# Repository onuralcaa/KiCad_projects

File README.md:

# Repository Hakkında 

Udemy - Donanım Tasarımı adlı eğitim çalışmaları.

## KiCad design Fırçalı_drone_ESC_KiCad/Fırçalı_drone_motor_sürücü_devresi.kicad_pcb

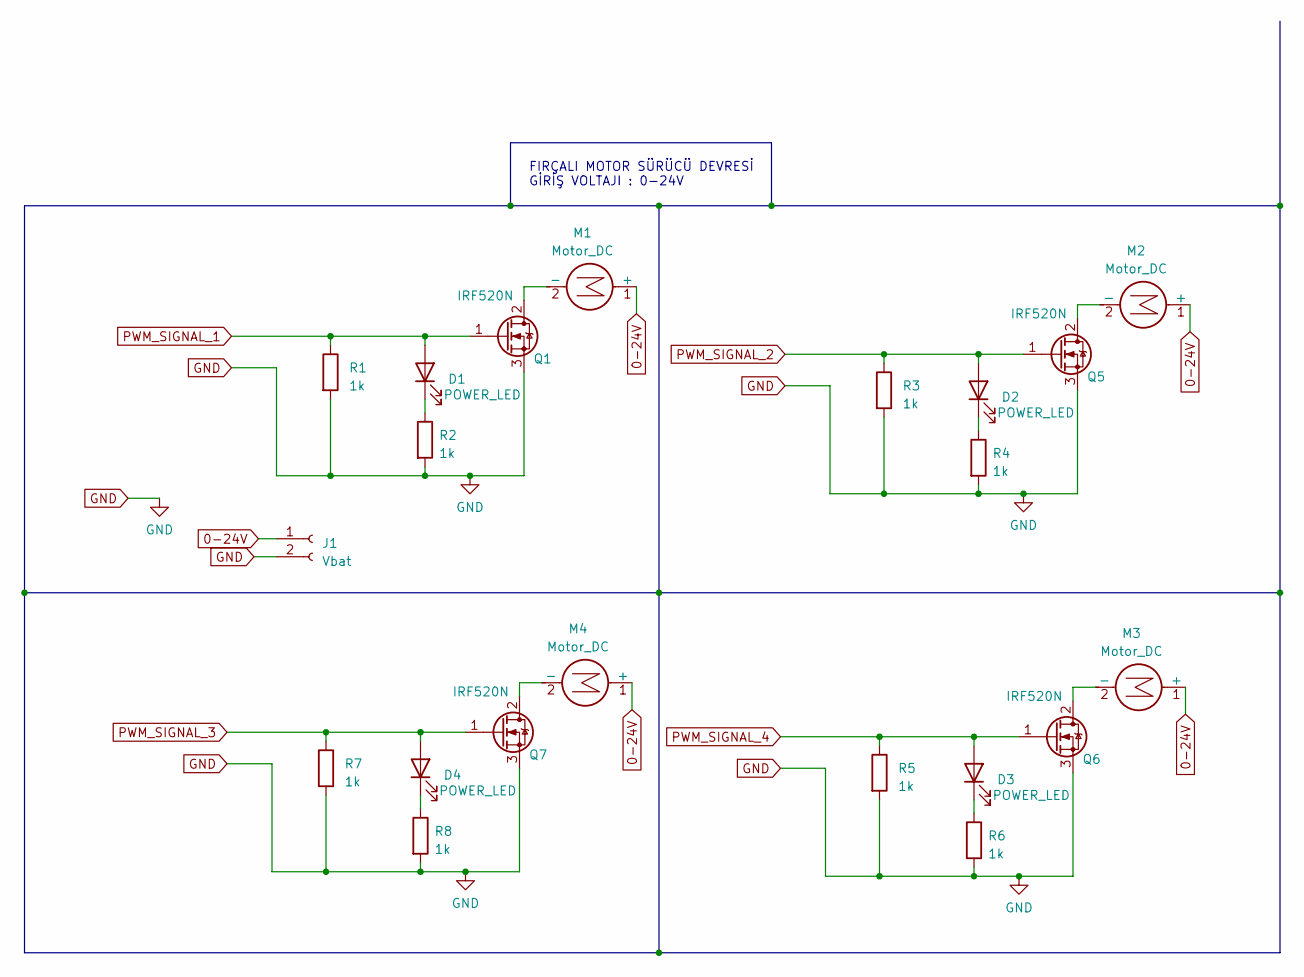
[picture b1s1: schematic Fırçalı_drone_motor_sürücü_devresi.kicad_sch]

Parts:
D1, D2, D3, D4: POWER_LED; D_DO-15_P2.54mm_Vertical_AnodeUp
J1: Vbat; PinHeader_1x02_P2.54mm_Vertical
M1, M2, M3, M4: Motor_DC; PinHeader_1x02_P2.54mm_Vertical
Q1, Q5, Q6, Q7: IRF520N; TO-220-3_Vertical
R1, R2, R3, R4, R5, R6, R7, R8: 1k; R_Axial_DIN0207_L6.3mm_D2.5mm_P7.62mm_Horizontal

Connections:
0-24V: J1.1, M1.1 (+), M2.1 (+), M3.1 (+), M4.1 (+)
GND: J1.2, Q1.3 (S), Q5.3 (S), Q6.3 (S), Q7.3 (S), R1.2, R2.2, R3.2, R4.2, R5.2, R6.2, R7.2, R8.2
unnamed: D1.1 (K), R2.1
unnamed: D2.1 (K), R4.1
unnamed: D3.1 (K), R6.1
unnamed: D4.1 (K), R8.1
unnamed: M1.2 (-), Q1.2 (D)
unnamed: M2.2 (-), Q5.2 (D)
unnamed: M3.2 (-), Q6.2 (D)
unnamed: M4.2 (-), Q7.2 (D)
PWM_SIGNAL_1: D1.2 (A), Q1.1 (G), R1.1
PWM_SIGNAL_2: D2.2 (A), Q5.1 (G), R3.1
PWM_SIGNAL_3: D4.2 (A), Q7.1 (G), R7.1
PWM_SIGNAL_4: D3.2 (A), Q6.1 (G), R5.1

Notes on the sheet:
FIRÇALI MOTOR SÜRÜCÜ DEVRESİ GİRİŞ VOLTAJI : 0-24V

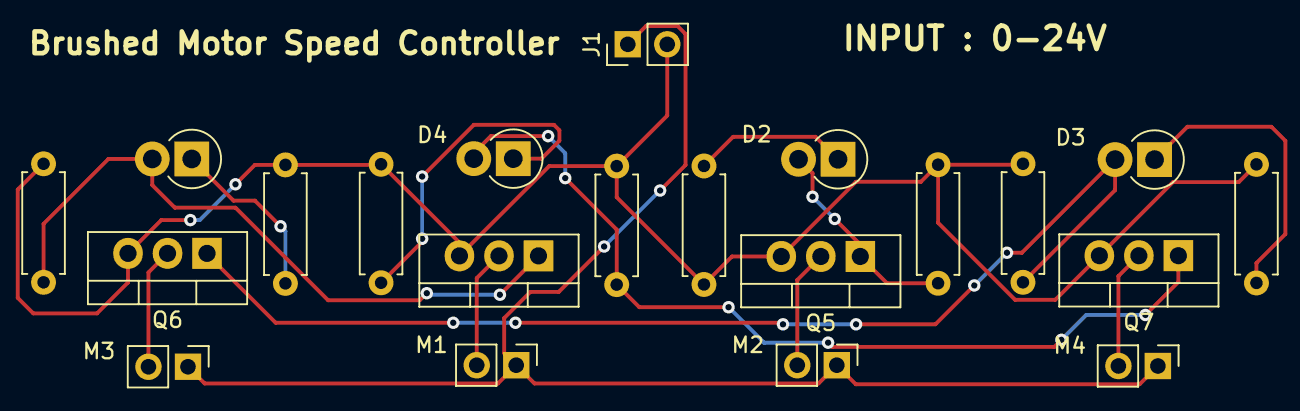
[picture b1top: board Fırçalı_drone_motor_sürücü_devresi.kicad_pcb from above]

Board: 2 copper layers, 21 parts (0 on the bottom side), 14 nets.

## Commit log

2023-10-21 STM32F405RTGx USB bağlantısı için gerekli olan kompenentler oluşturuldu.
2023-11-17 Brushed Motor Driver
2023-11-22 The schematic part of the board is completed.
2023-11-22 Schematic image added.
